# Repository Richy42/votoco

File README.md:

# Voron Tool Controller
A 3D printer controller board

Inspired by the possibility of Klipper 3D printer firmware (https://www.klipper3d.org/) that allows to have several I/O controller boards, Voron Tool Controller is a small board intended to be mounted on the moving print head assembly of a Voron 3D printer.

This reduces the cabling effort significantly as only power supply and CAN is needed.

PrintHeadController has the following features:
* Based on STM32 , so it is supported by the Klipper firmware out of the box
* TMC2209 on board for the extruder
* Supports the UART configuration of TMC driver
* 12 V and 24 V capable
* 2 Digital inputs
* 3 MOSFET outputs (e.g. hotend heater, fans)
* 1 Thermistor inputs
* BLTouch support
* Debug pins accessible
* Accelerometer ADXL245
* Don't Touch It connector (https://github.com/Richy42/DontTouchIt)

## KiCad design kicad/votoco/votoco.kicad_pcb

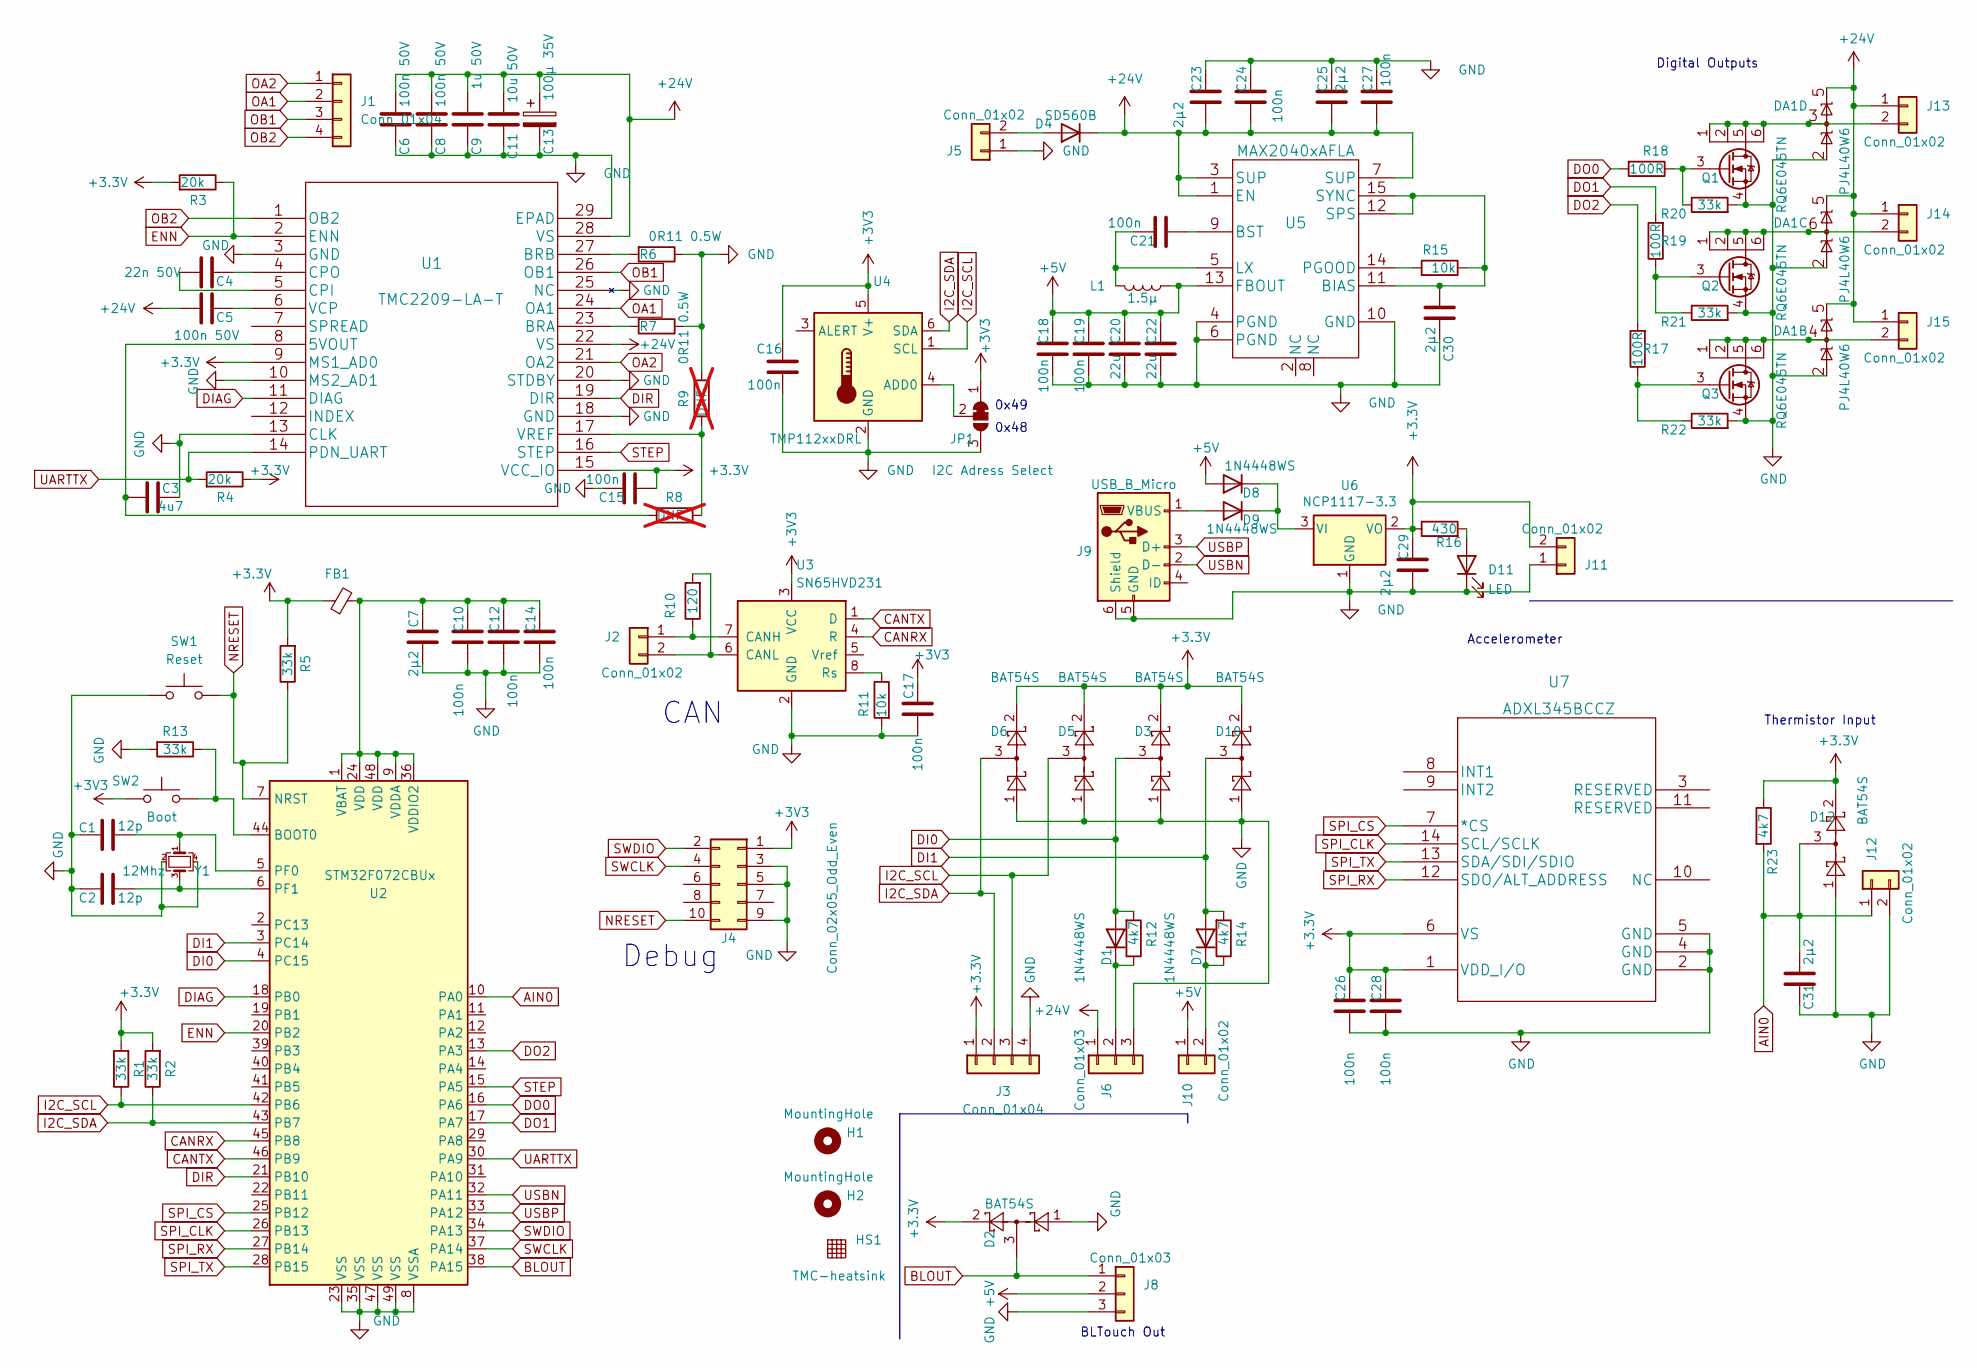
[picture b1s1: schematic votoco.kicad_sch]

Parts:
C1, C2: 12p; C_0603_1608Metric
C3: 4u7; C_0603_1608Metric
C4: 22n 50V; C_0603_1608Metric
C5, C6, C8: 100n 50V; C_0603_1608Metric
C7, C23, C25, C29, C30, C31: 2µ2; C_0603_1608Metric
C9: 1u 50V; C_0603_1608Metric
C10, C12, C14, C15, C16, C17, C18, C19, C21, C24, C26, C27, C28: 100n; C_0603_1608Metric
C11: 10u 50V; C_0603_1608Metric
C13: 100µ 35V; CP_Elec_6.3x7.7
C20, C22: 22u; C_0603_1608Metric
D1, D7, D8, D9: 1N4448WS; D_SOD-323
D2, D3, D5, D6, D10, D12: BAT54S; SOT-23
D4: SD560B; D_SMB
D11: LED; LED_0603_1608Metric
DA1: PJ4L40W6; SOT-23-6
FB1: FerriteBead_Small; L_0603_1608Metric
H1, H2: MountingHole; MountingHole_3.2mm_M3
HS1: TMC-heatsink
J1, J3: Conn_01x04; JST_PH_B4B-PH-SM4-TB_1x04-1MP_P2.00mm_Vertical
J2, J10, J11, J12, J13, J14, J15: Conn_01x02; JST_PH_B2B-PH-SM4-TB_1x02-1MP_P2.00mm_Vertical
J4: Conn_02x05_Odd_Even; PinHeader_2x05_P1.27mm_Vertical_SMD
J5: Conn_01x02; JST_VH_B2P-VH-B_1x02_P3.96mm_Vertical
J6, J8: Conn_01x03; JST_PH_B3B-PH-SM4-TB_1x03-1MP_P2.00mm_Vertical
J9: USB_B_Micro; USB_Micro-B_Wuerth_614105150721_Vertical_CircularHoles
JP1: I2C Adress Select; SolderJumper-3_P1.3mm_Bridged12_RoundedPad1.0x1.5mm
L1: 1.5µ; L_0805_2012Metric
Q1, Q2, Q3: RQ6E045TN; SOT-457T
R1, R2, R5, R13, R20, R21, R22: 33k; R_0603_1608Metric
R3, R4: 20k; R_0603_1608Metric
R6, R7: 0R11 0.5W; R_0805_2012Metric
R8, R9: DNF; R_0603_1608Metric; not fitted
R10: 120; R_0603_1608Metric
R11, R15: 10k; R_0603_1608Metric
R12, R14, R23: 4k7; R_0603_1608Metric
R16: 430; R_0603_1608Metric
R17, R18, R19: 100R; R_0603_1608Metric
SW1: Reset; SW_Push_1P1T-Pana_EVPAA
SW2: Boot; SW_Push_1P1T-Pana_EVPAA
U1: TMC2209-LA-T
U2: STM32F072CBUx; UFQFPN-48_EP_7x7_Pitch0.5mm
U3: SN65HVD231; SOIC-8_3.9x4.9mm_P1.27mm
U4: TMP112xxDRL; SOT-563
U5: MAX2040xAFLA; MAX2040xAFL
U6: NCP1117-3.3; SOT-223-3_TabPin2
U7: ADXL345BCCZ
Y1: 12Mhz; Crystal_SMD_2520-4Pin_2.5x2.0mm

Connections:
+5V: C18.1, C19.1, C20.2, C22.2, D8.2 (A), J8.2, J10.1, L1.1, U5.13 (FBOUT)
+24V: C5.2, C6.1, C8.1, C9.1, C11.1, C13.1, C23.2, C24.2, C25.2, C27.2, D4.1 (K), DA1.5, J6.1, J13.1, J14.1, J15.1, U1.22 (VS), U1.28 (VS), U5.1 (EN), U5.3 (SUP), U5.7 (SUP)
AIN0: C31.1, D12.3, J12.1, R23.2, U2.10 (PA0)
BLOUT: D2.3, J8.1, U2.38 (PA15)
CANRX: U2.45 (PB8), U3.4 (R)
CANTX: U2.46 (PB9), U3.1 (D)
DI0: D1.2 (A), D3.3, R12.2, U2.4 (PC15)
DI1: D7.2 (A), D10.3, R14.2, U2.3 (PC14)
DIAG: U1.11 (DIAG), U2.18 (PB0)
DIR: U1.19 (DIR), U2.21 (PB10)
DO0: R18.2, U2.16 (PA6)
DO1: R19.2, U2.17 (PA7)
DO2: R17.2, U2.13 (PA3)
ENN: R3.1, U1.2 (ENN), U2.20 (PB2)
GND: C1.1, C2.1, C3.1, C6.2, C7.2, C8.2, C9.2, C10.2, C11.2, C12.2, C13.2, C14.2, C15.1, C16.2, C17.2, C18.2, C19.2, C20.1, C22.1, C23.1, C24.1, C25.1, C26.2, C27.1, C28.2, C29.2, C30.2, C31.2, D2.1, D3.1, D5.1, D6.1, D10.1, D11.1 (K), D12.1, DA1.2, J3.4, J4.3, J4.5, J4.9, J5.1, J6.3, J8.3, J9.5 (GND), J9.6 (Shield), J11.1, J12.2, JP1.3 (B), Q1.4 (S), Q2.4 (S), Q3.4 (S), R6.1, R7.1, R9.2, R11.2, R13.2, R20.2, R21.2, R22.2, SW1.1, U1.3 (GND), U1.10 (MS2_AD1), U1.13 (CLK), U1.18 (GND), U1.20 (STDBY), U1.25 (NC), U1.29 (EPAD), U2.8 (VSSA), U2.23 (VSS), U2.35 (VSS), U2.47 (VSS), U2.49 (VSS), U3.2 (GND), U4.2 (GND), U5.4 (PGND), U5.6 (PGND), U5.10 (GND), U6.1 (GND), U7.2 (GND), U7.4 (GND), U7.5 (GND), Y1.2, Y1.4
I2C_SCL: D5.3, J3.3, R1.1, U2.42 (PB6), U4.1 (SCL)
I2C_SDA: D6.3, J3.2, R2.1, U2.43 (PB7), U4.6 (SDA)
NRESET: J4.10, R5.1, SW1.2, U2.7 (NRST)
unnamed: D1.1 (K), J6.2, R12.1
unnamed: D4.2 (A), J5.2
unnamed: D7.1 (K), J10.2, R14.1
unnamed: D8.1 (K), D9.1 (K), U6.3 (VI)
unnamed: D9.2 (A), J9.1 (VBUS)
unnamed: D11.2 (A), R16.2
unnamed: J2.1, R10.1, U3.7 (CANH)
unnamed: J2.2, R10.2, U3.6 (CANL)
unnamed: DA1.3, J13.2, Q1.1 (D), Q1.2 (D), Q1.5 (D), Q1.6 (D)
unnamed: DA1.6, J14.2, Q2.1 (D), Q2.2 (D), Q2.5 (D), Q2.6 (D)
unnamed: DA1.4, J15.2, Q3.1 (D), Q3.2 (D), Q3.5 (D), Q3.6 (D)
unnamed: JP1.2 (C), U4.4 (ADD0)
unnamed: Q1.3 (G), R18.1, R20.1
unnamed: Q2.3 (G), R19.1, R21.1
unnamed: Q3.3 (G), R17.1, R22.1
unnamed: C3.2, R8.1, U1.8 (5VOUT)
unnamed: R7.2, U1.23 (BRA)
unnamed: R6.2, U1.27 (BRB)
unnamed: C4.2, U1.5 (CPI)
unnamed: C4.1, U1.4 (CPO)
unnamed: C5.1, U1.6 (VCP)
unnamed: R8.2, R9.1, U1.17 (VREF)
unnamed: R13.1, SW2.2, U2.44 (BOOT0)
unnamed: C1.2, U2.5 (PF0), Y1.1
unnamed: C2.2, U2.6 (PF1), Y1.3
unnamed: C7.1, C10.1, C12.1, C14.1, FB1.2, U2.1 (VBAT), U2.9 (VDDA), U2.24 (VDD), U2.36 (VDDIO2), U2.48 (VDD)
unnamed: R11.1, U3.8 (Rs)
unnamed: C30.1, R15.1, U5.11 (BIAS), U5.12 (SPS), U5.15 (SYNC)
unnamed: C21.2, U5.9 (BST)
unnamed: C21.1, L1.2, U5.5 (LX)
unnamed: R15.2, U5.14 (PGOOD)
OA1: J1.2, U1.24 (OA1)
OA2: J1.1, U1.21 (OA2)
OB1: J1.3, U1.26 (OB1)
OB2: J1.4, U1.1 (OB2)
SPI_CLK: U2.26 (PB13), U7.14 (SCL/SCLK)
SPI_CS: U2.25 (PB12), U7.7 (*CS)
SPI_RX: U2.27 (PB14), U7.12 (SDO/ALT_ADDRESS)
SPI_TX: U2.28 (PB15), U7.13 (SDA/SDI/SDIO)
STEP: U1.16 (STEP), U2.15 (PA5)
SWCLK: J4.4, U2.37 (PA14)
SWDIO: J4.2, U2.34 (PA13)
UARTTX: R4.2, U1.14 (PDN_UART), U2.30 (PA9)
USBN: J9.2 (D-), U2.32 (PA11)
USBP: J9.3 (D+), U2.33 (PA12)

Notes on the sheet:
BLTouch Out
Thermistor Input
Debug
CAN
Accelerometer
Digital Outputs
0x48
0x49

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
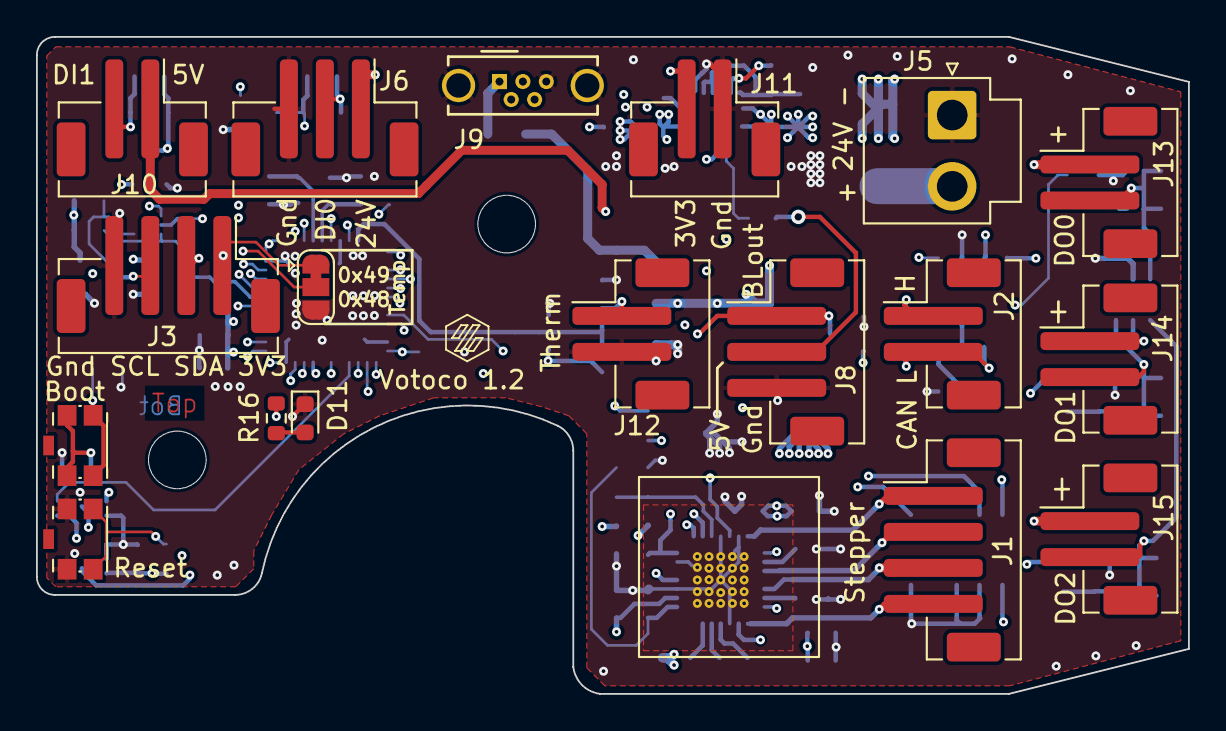
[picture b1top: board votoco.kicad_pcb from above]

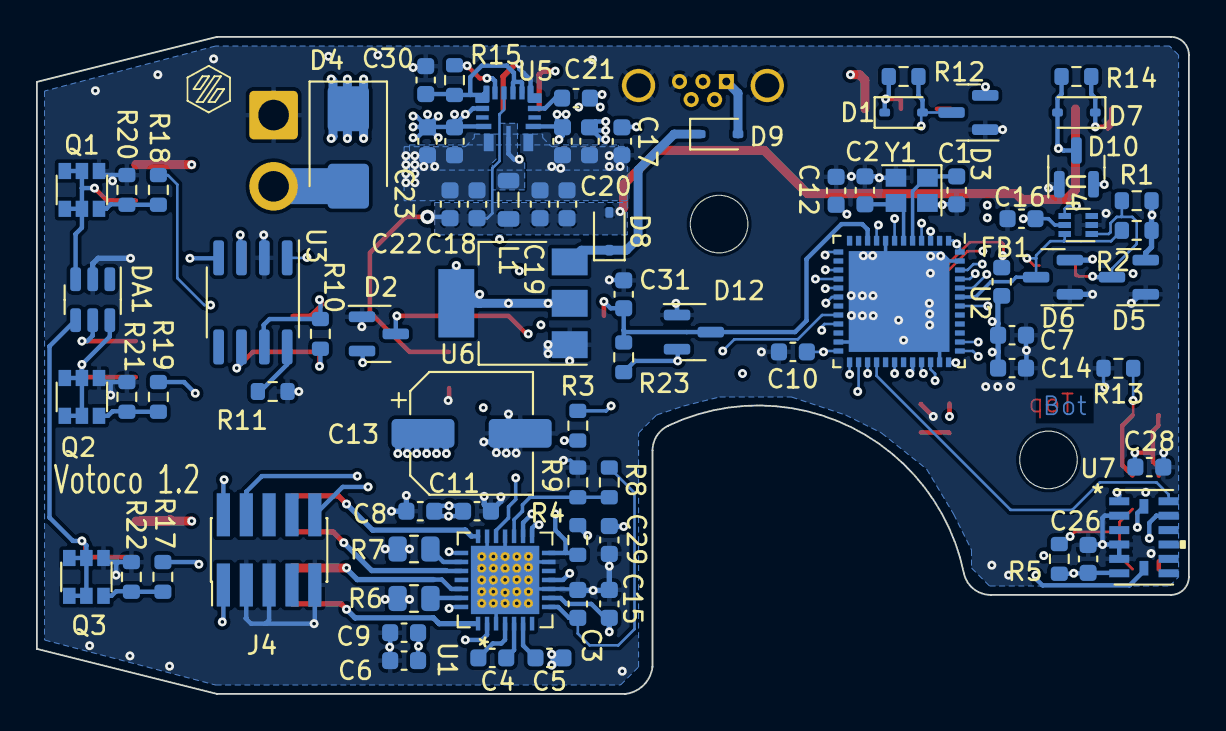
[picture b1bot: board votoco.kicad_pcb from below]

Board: 4 copper layers, 64.0 x 36.5 mm, 100 parts (79 on the bottom side), 64 nets.

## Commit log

2023-04-05 some error from V1.0 corrected
2023-05-26 switched to new mcu
2023-06-08 temp sensor added / I2C connector added / layout almost finished
2023-06-09 warning clean-up
2023-06-09 warning clean-up finished
2023-06-17 boot0 pull-down-added / uart-tx corrected
2023-06-17 V1.1 fabrication files generated
2023-10-26 footprint corrected / DIR - SPI clk pins exchanged

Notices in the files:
parts and their libraries:
Copyright 2021 Accelerated Designs. All rights reserved.
